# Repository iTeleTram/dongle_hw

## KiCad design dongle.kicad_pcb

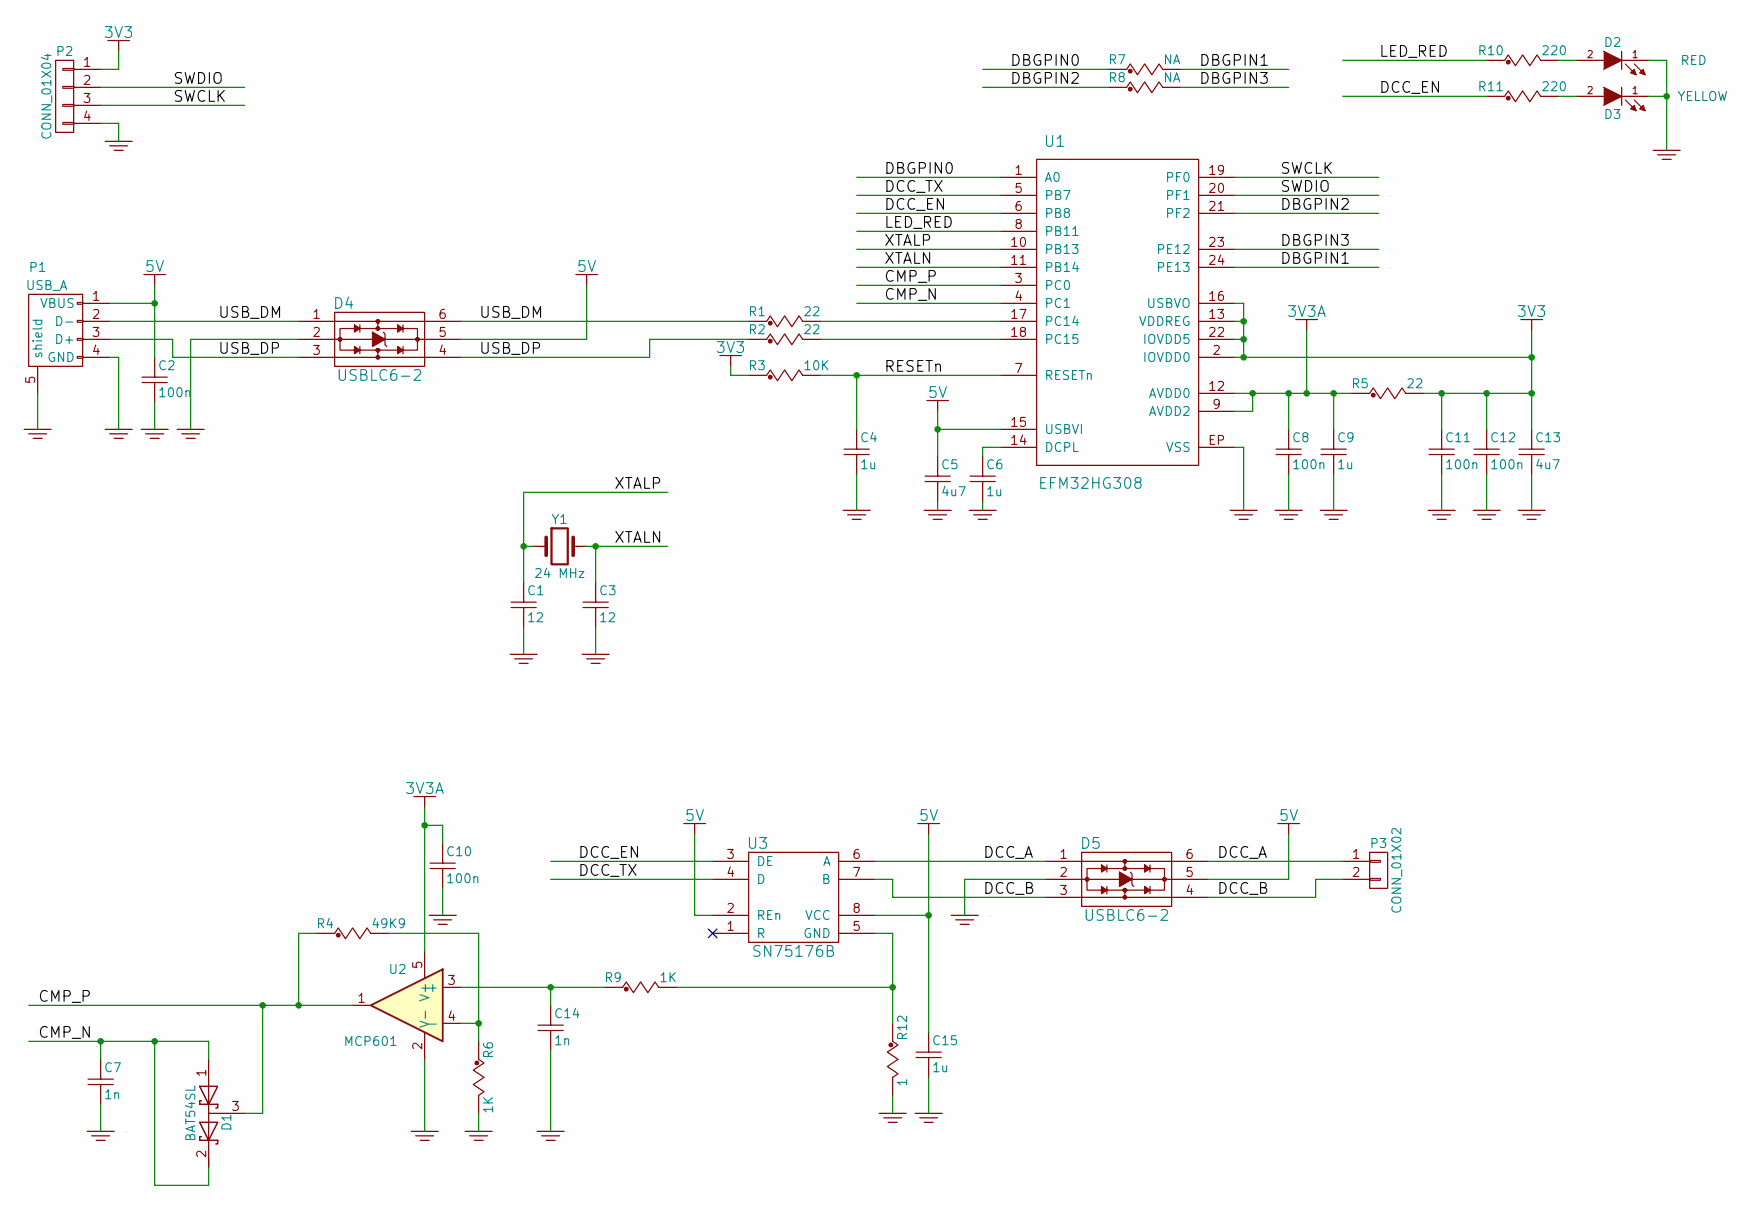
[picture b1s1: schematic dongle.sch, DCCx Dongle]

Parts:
C1, C3: 12; C_0603; Voltage Volt; mfg_pn CC0603JRNPO9BN120
C2, C8, C10, C11, C12: 100n; C_0603; Voltage Volt; mfg_pn 06033C104K4T2A
C4, C6, C9, C15: 1u; C_0603; Voltage Volt; mfg_pn 0603ZG105ZAT2A
C5, C13: 4u7; C_0603; Voltage Volt; mfg_pn GRM188R60J475KE19J
C7, C14: 1n; C_0603; Voltage Volt; mfg_pn 885012206083
D1: BAT54SL; SOT-23; mfg_pn BAT54SLT1G
D2: RED; LED_0603; mfg_pn APT1608SRCPRV
D3: YELLOW; LED_0603; mfg_pn APT1608SYCK
D4, D5: USBLC6-2; SOT-23-6; mfg_pn USBLC6-2SC6
P1: USB_A; usb_plug_th; mfg_pn 48037-0001
P2: CONN_01X04; Socket_Strip_Straight_1x04
P3: CONN_01X02; Socket_Strip_Straight_1x02
R1, R2, R5: 22; R_0603; mfg_pn CRCW060322R0FKEA
R3: 10K; R_0603; mfg_pn CRCW060310K0FKEA
R4: 49K9; R_0603; mfg_pn CRCW060349K9FKEA
R6, R9: 1K; R_0603; mfg_pn CRCW06031K00FKEA
R7, R8: NA; R_0603
R10, R11: 220; R_0603; mfg_pn CRCW0603220RFKEA
R12: 1; R_0603; mfg_pn CRCW06031R00FKEA
U1: EFM32HG308; QFN24_5mm; mfg_pn EFM32HG308F32G-B-QFN24
U2: MCP601; SOT-23-5; mfg_pn MCP601RT-I/OT
U3: SN75176B; SOIC-8_3.9x4.9mm_Pitch1.27mm; mfg_pn SN75176BDRG4
Y1: 24 MHz; Crystal_SMD_3225-4pin_3.2x2.5mm; mfg_pn FA-238 24.0000MB-C3

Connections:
3V3: C11.2, C12.2, C13.2, P2.1, R3.1, R5.2, U1.2 (IOVDD0), U1.13 (VDDREG), U1.16 (USBVO), U1.22 (IOVDD5)
3V3A: C8.2, C9.2, C10.2, R5.1, U1.9 (AVDD2), U1.12 (AVDD0), U2.5 (V+)
5V: C2.2, C5.2, C15.2, D4.5 (Vbus), D5.5 (Vbus), P1.1 (VBUS), U1.15 (USBVI), U3.2 (REn), U3.8 (VCC)
/CMP_N: C7.2, D1.1 (A), D1.2 (K), U1.4 (PC1)
/CMP_P: D1.3 (common), R4.1, U1.3 (PC0), U2.1
/DBGPIN0: R7.1, U1.1 (A0)
/DBGPIN1: R7.2, U1.24 (PE13)
/DBGPIN2: R8.1, U1.21 (PF2)
/DBGPIN3: R8.2, U1.23 (PE12)
/DCC_A: D5.1 (IO1), D5.6 (IO1), P3.1, U3.6 (A)
/DCC_B: D5.3 (IO2), D5.4 (IO2), P3.2, U3.7 (B)
/DCC_EN: R11.1, U1.6 (PB8), U3.3 (DE)
/DCC_TX: U1.5 (PB7), U3.4 (D)
/LED_RED: R10.1, U1.8 (PB11)
/RESETn: C4.2, R3.2, U1.7 (RESETn)
/SWCLK: P2.3, U1.19 (PF0)
/SWDIO: P2.2, U1.20 (PF1)
/USB_DM: D4.1 (IO1), D4.6 (IO1), P1.2 (D-), R1.1
/USB_DP: D4.3 (IO2), D4.4 (IO2), P1.3 (D+), R2.1
/XTALN: C3.2, U1.11 (PB14), Y1.3
/XTALP: C1.2, U1.10 (PB13), Y1.1
GND: C1.1, C2.1, C3.1, C4.1, C5.1, C6.1, C7.1, C8.1, C9.1, C10.1, C11.1, C12.1, C13.1, C14.1, C15.1, D2.1 (K), D3.1 (K), D4.2 (GND), D5.2 (GND), P1.4 (GND), P1.5 (shield), P2.4, R6.2, R12.2, U1.EP (VSS), U2.2 (V-)
unnamed: C6.2, U1.14 (DCPL)
unnamed: C14.2, R9.1, U2.3 (+)
unnamed: D2.2 (A), R10.2
unnamed: D3.2 (A), R11.2
unnamed: R1.2, U1.17 (PC14)
unnamed: R2.2, U1.18 (PC15)
unnamed: R4.2, R6.1, U2.4 (-)
unnamed: R9.2, R12.1, U3.5 (GND)

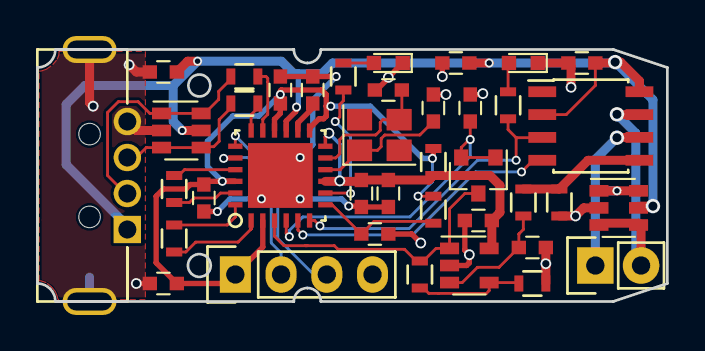
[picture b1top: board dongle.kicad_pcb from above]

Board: 2 copper layers, 35.0 x 14.0 mm, 39 parts (0 on the bottom side), 30 nets.
